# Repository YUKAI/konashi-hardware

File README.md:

# konashi Hardware Libraries

## What
[konashi](http://konashi.ux-xu.com/)と拡張ボードで電子工作するときに役立つデータです。

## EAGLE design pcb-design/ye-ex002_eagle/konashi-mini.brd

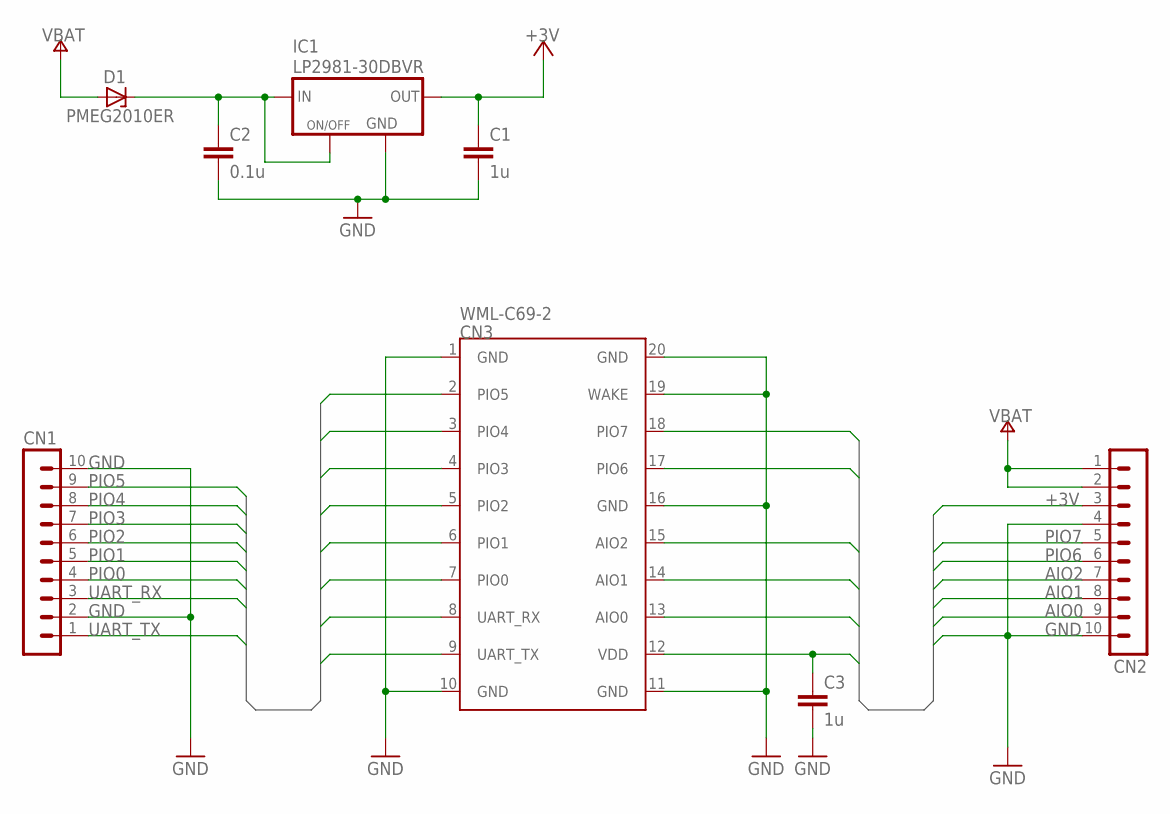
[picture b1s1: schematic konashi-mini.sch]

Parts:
C1, C3: 1u; C0603
C2: 0.1u; C0603
CN1, CN2: MA10-1_LARGE
CN3: WML-C69-2; WML-C69
D1: PMEG2010ER; SOD123-W
IC1: LP2981-30DBVR; SOT-23

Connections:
+3V: C1.1, C3.1, CN2.3, CN3.12 (VDD), IC1.5 (OUT)
AIO0: CN2.9, CN3.13 (AIO0)
AIO1: CN2.8, CN3.14 (AIO1)
AIO2: CN2.7, CN3.15 (AIO2)
GND: C1.2, C2.2, C3.2, CN1.2, CN1.10, CN2.4, CN2.10, CN3.1 (GND), CN3.10 (GND), CN3.11 (GND), CN3.16 (GND), CN3.19 (WAKE), CN3.20 (GND), IC1.2 (GND)
unnamed: C2.1, D1.K (C), IC1.1 (IN), IC1.3 (ON/OFF)
PIO0: CN1.4, CN3.7 (PIO0)
PIO1: CN1.5, CN3.6 (PIO1)
PIO2: CN1.6, CN3.5 (PIO2)
PIO3: CN1.7, CN3.4 (PIO3)
PIO4: CN1.8, CN3.3 (PIO4)
PIO5: CN1.9, CN3.2 (PIO5)
PIO6: CN2.6, CN3.17 (PIO6)
PIO7: CN2.5, CN3.18 (PIO7)
UART_RX: CN1.3, CN3.8 (UART_RX)
UART_TX: CN1.1, CN3.9 (UART_TX)
VBATT: CN2.1, CN2.2, D1.A

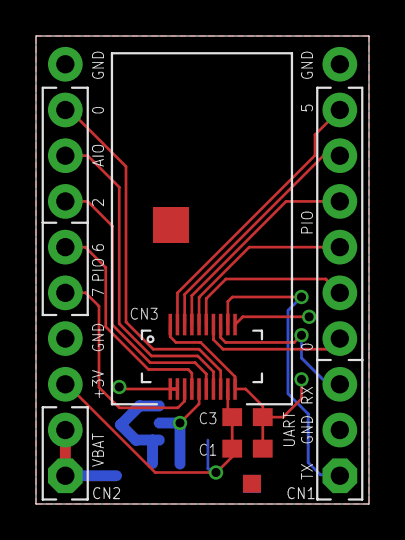
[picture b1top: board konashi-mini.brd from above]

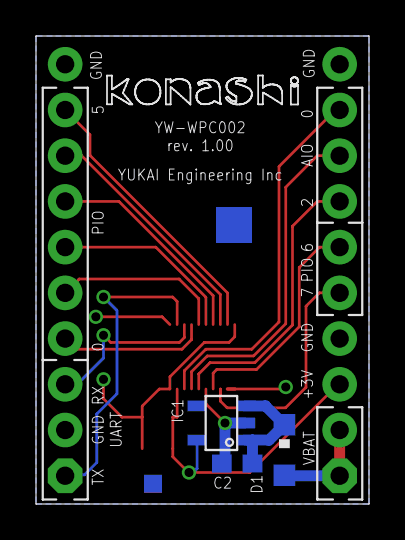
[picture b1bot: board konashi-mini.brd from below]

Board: 2 copper layers, 18.5 x 26.0 mm, 9 parts (4 on the bottom side), 17 nets.

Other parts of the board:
U$4: KONASHI_LOGO_WIRE_MINI

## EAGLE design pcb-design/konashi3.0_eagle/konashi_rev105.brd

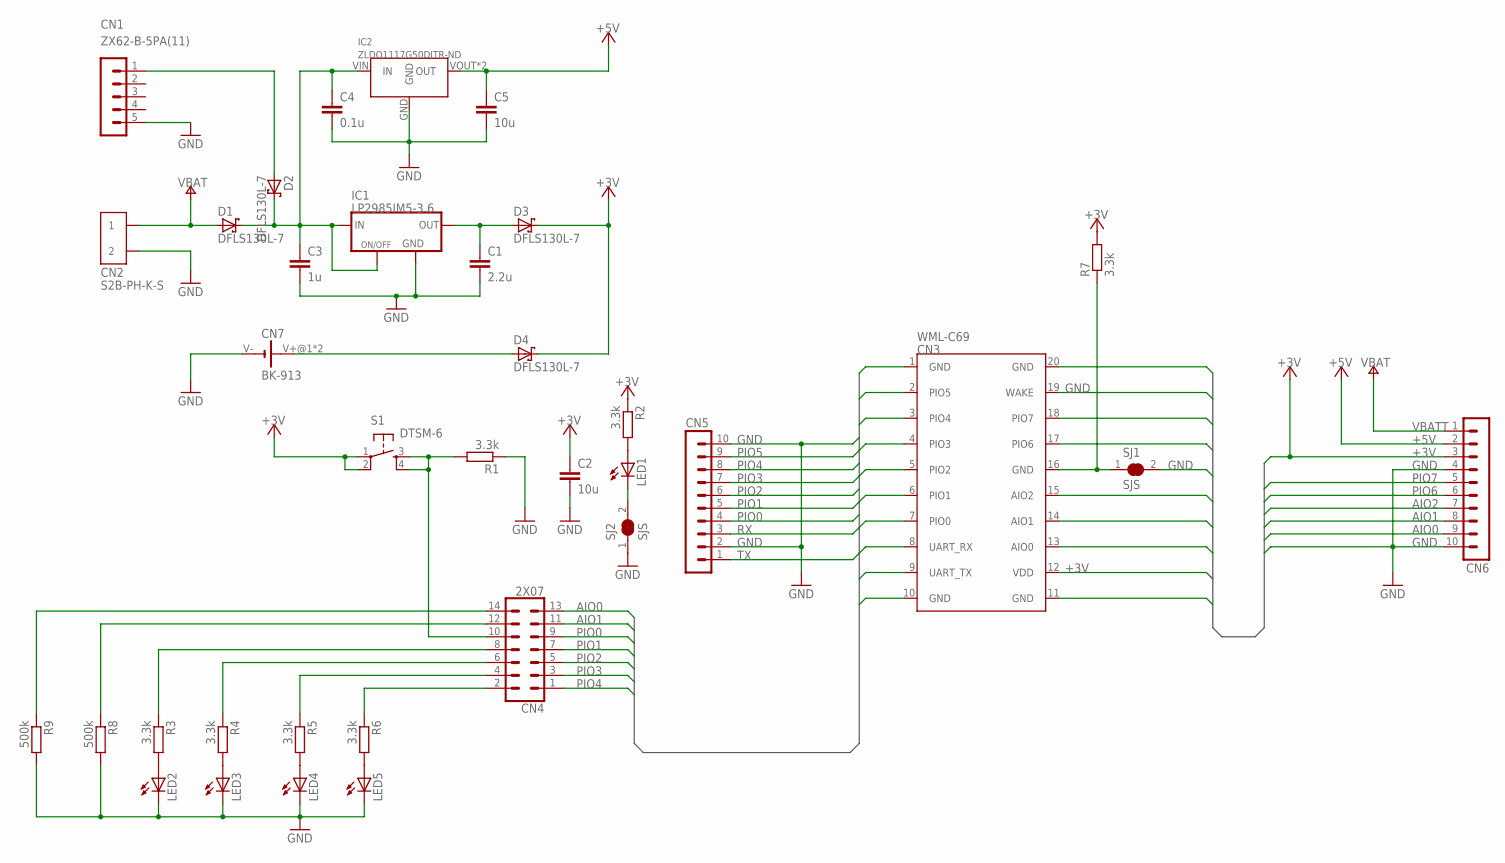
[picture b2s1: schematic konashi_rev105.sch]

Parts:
C1: 2.2u; C0603
C2, C5: 10u; C0603
C3: 1u; C0603
C4: 0.1u; C0603
CN1: ZX62-B-5PA(11); MICRO-B
CN2: S2B-PH-K-S
CN3: WML-C69
CN4: 2X07
CN5, CN6: MA10-1
CN7: BK-913
D1, D2, D3, D4: DFLS130L-7; DFLS130L
IC1: LP2985IM5-3.6; SOT-23
IC2: ZLDO1117G50DITR-ND; SOD233
LED1, LED2, LED3, LED4, LED5: LEDCHIPLED_1206; CHIPLED_1206
R1, R2, R3, R4, R5, R6, R7: 3.3k; R0603
R8, R9: 500k; R0603
S1: DTSM-6
SJ1, SJ2: SJS

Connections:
+3V: C2.1, CN3.12 (VDD), CN6.3, D3.C, D4.C, R2.1, R7.2, S1.1, S1.2
+5V: C5.1, CN6.2, IC2.VOUT (OUT), IC2.VOUT2 (OUT)
AIO0: CN3.13 (AIO0), CN4.13, CN6.9
AIO1: CN3.14 (AIO1), CN4.11, CN6.8
AIO2: CN3.15 (AIO2), CN6.7
GND: C1.2, C2.2, C3.2, C4.2, C5.2, CN1.5 (5.GND), CN2.P$2 (2), CN3.1 (GND), CN3.10 (GND), CN3.11 (GND), CN3.19 (WAKE), CN3.20 (GND), CN5.2, CN5.10, CN6.4, CN6.10, CN7.V- (-), IC1.2 (GND), IC2.GND, LED2.C, LED3.C, LED4.C, LED5.C, R1.1, R8.2, R9.2, SJ1.2, SJ2.1
unnamed: LED3.A, R4.2
unnamed: LED2.A, R3.2
unnamed: LED1.C, SJ2.2
unnamed: CN7.V+@1 (+), CN7.V+@2 (+), D4.A
unnamed: CN3.16 (GND), R7.1, SJ1.1
unnamed: C1.1, D3.A, IC1.5 (OUT)
unnamed: CN4.12, R8.1
unnamed: C3.1, C4.1, D1.C, D2.C, IC1.1 (IN), IC1.3 (ON/OFF), IC2.VIN (IN)
unnamed: LED5.A, R6.2
unnamed: LED4.A, R5.2
unnamed: CN4.14, R9.1
unnamed: LED1.A, R2.2
unnamed: CN4.10, R1.2, S1.3, S1.4
unnamed: CN4.6, R4.1
unnamed: CN4.2, R6.1
unnamed: CN4.4, R5.1
unnamed: CN4.8, R3.1
unnamed: CN1.1 (1.VBUS), D2.A
PIO0: CN3.7 (PIO0), CN4.9, CN5.4
PIO1: CN3.6 (PIO1), CN4.7, CN5.5
PIO2: CN3.5 (PIO2), CN4.5, CN5.6
PIO3: CN3.4 (PIO3), CN4.3, CN5.7
PIO4: CN3.3 (PIO4), CN4.1, CN5.8
PIO5: CN3.2 (PIO5), CN5.9
PIO6: CN3.17 (PIO6), CN6.6
PIO7: CN3.18 (PIO7), CN6.5
RX: CN3.8 (UART_RX), CN5.3
TX: CN3.9 (UART_TX), CN5.1
VBATT: CN2.P$1 (1), CN6.1, D1.A

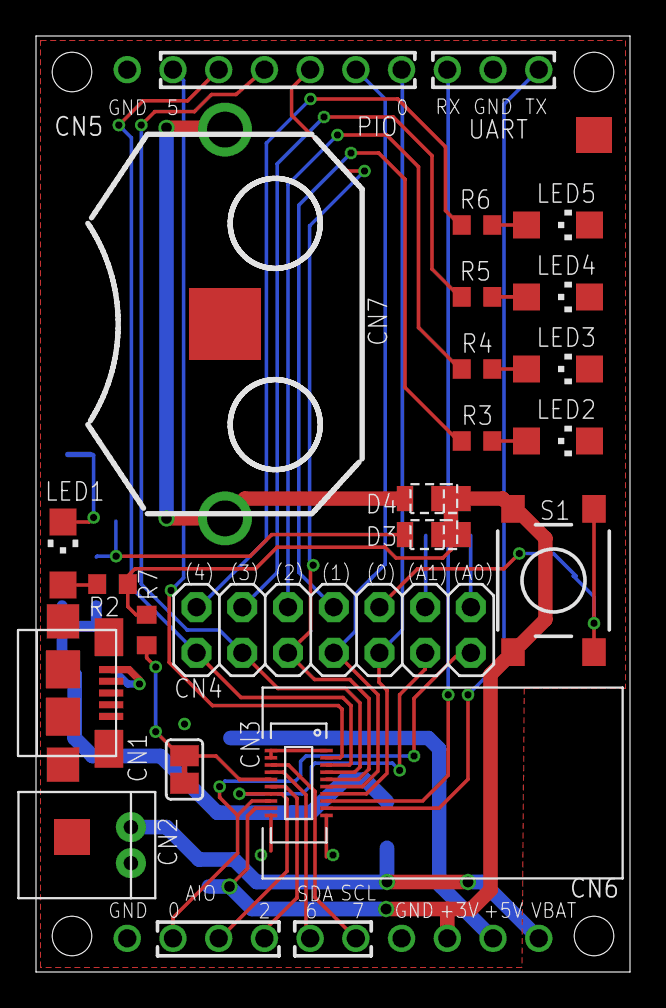
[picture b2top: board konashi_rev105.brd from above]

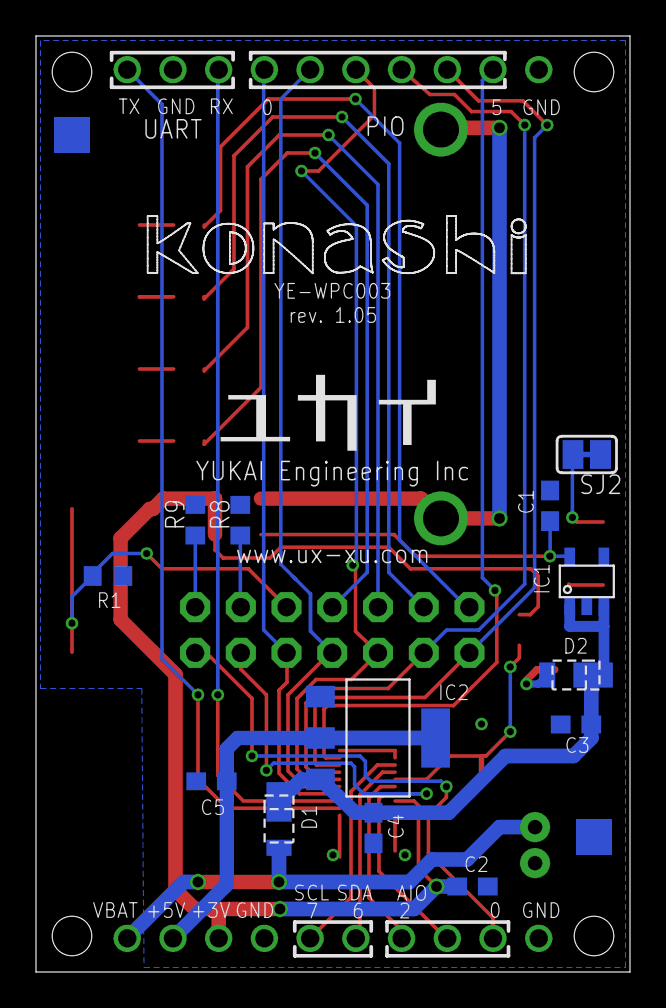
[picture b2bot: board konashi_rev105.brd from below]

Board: 2 copper layers, 33.0 x 52.0 mm, 37 parts (15 on the bottom side), 35 nets.

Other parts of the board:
U$13: KONASHI_LOGO_WIRE
U$14: YUKAILOGO

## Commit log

2017-03-09 Initial commitment
2017-03-09 Added readme
2017-03-09 Reviewed directory structure
2017-03-09 Moved files
2017-07-20 Add konashi base board's design and production data
2017-07-21 konashi3.0_eagle追加
2017-07-24 500kohm追加、ジャンパ用ピンヘッダ変更
2017-07-24 シルク修正
2017-07-25 ジャンパピンシルク追加等
2017-07-25 ガーバーデータ追加、レギュレータ型番変更
2017-07-25 BOM追加
2019-04-18 Added logo and konashi3 eagle library
2019-10-29 Added konashi mini
2019-10-29 Add fritzing
2019-10-29 Add YE-EX001 gerber
